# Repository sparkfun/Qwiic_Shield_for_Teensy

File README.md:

# Qwiic_Shield_for_Teensy
This is a shield that connects the I2C bus on a Teensy to Qwiic connectors.

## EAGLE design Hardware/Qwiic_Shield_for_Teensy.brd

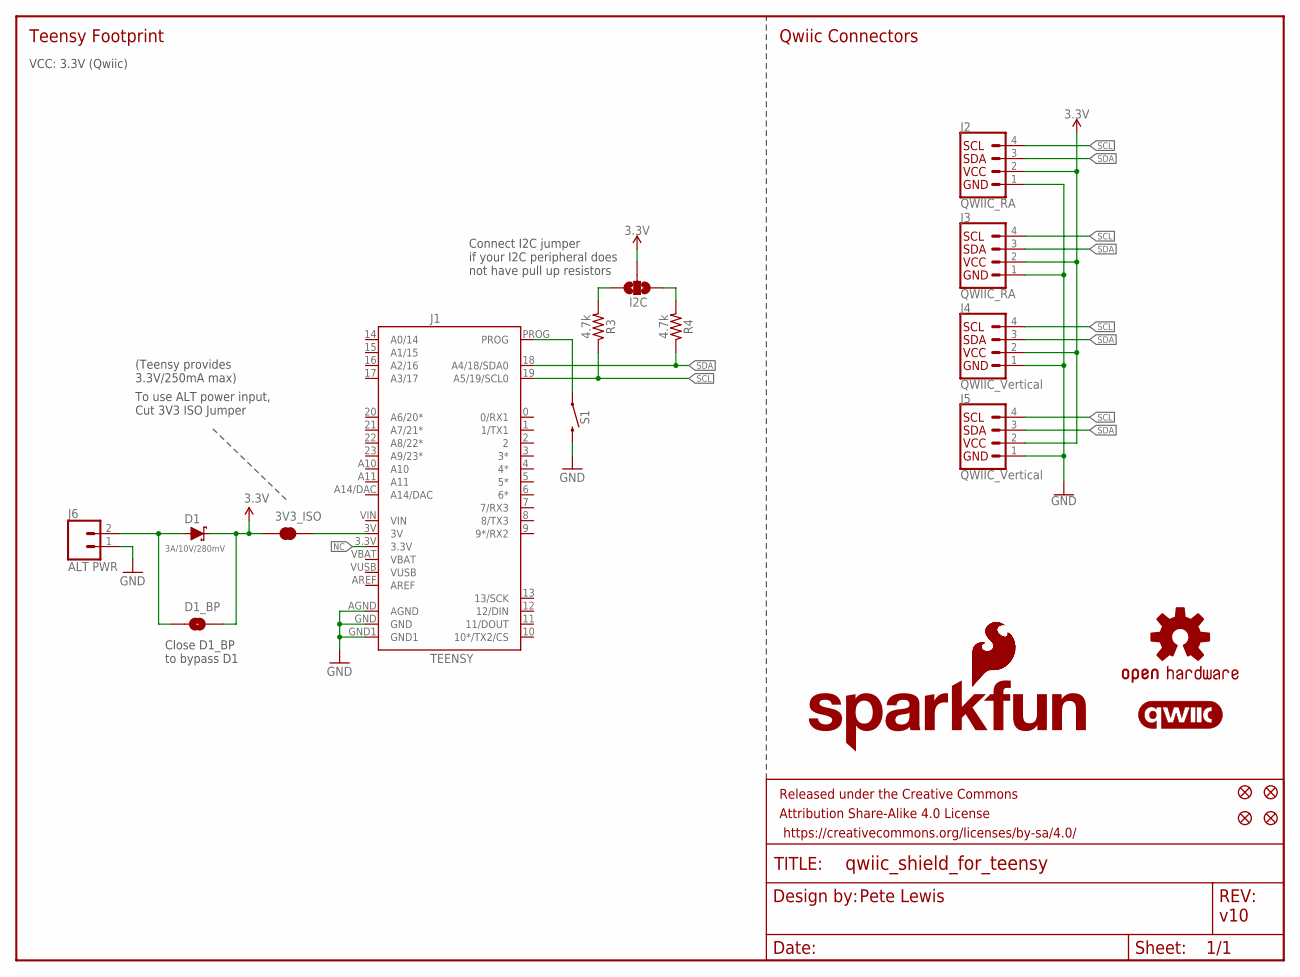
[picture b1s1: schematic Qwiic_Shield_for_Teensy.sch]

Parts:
3V3_ISO: JUMPER-SMT_2_NC_TRACE_SILK; SMT-JUMPER_2_NC_TRACE_SILK
D1: 3A/10V/280mV; SOD-323
D1_BP: JUMPER-SMT_2_NO_SILK; SMT-JUMPER_2_NO_SILK
FD1, FD2, FD3, FD4: FIDUCIAL1X2; FIDUCIAL-1X2
FRAME1: FRAME-LETTER; CREATIVE_COMMONS
I2C: JUMPER-SMT_3_NO_SILK; SMT-JUMPER_3_NO_SILK
J1: TEENSY; TEENSY_NOSILK
J2, J3: QWIIC_RA; JST04_1MM_RA
J4, J5: QWIIC_Vertical; JST04_1MM_VERT
J6: ALT PWR; 1X02_NO_SILK
LOGO1: SFE_LOGO_NAME_FLAME.1_INCH; SFE_LOGO_NAME_FLAME_.1
LOGO2: SFE_LOGO_FLAME.1_INCH; SFE_LOGO_FLAME_.1
LOGO3: OSHW-LOGOS; OSHW-LOGO-S
LOGO4: QWIIC_LOGO_5MM; QWIIC_5MM
R3, R4: 4.7k; 0603
S1: SMD_5.2MM; TACTILE_SWITCH_SMD_5.2MM

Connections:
3.3V: 3V3_ISO.1, D1.C, D1_BP.2, I2C.2, J2.2, J3.2, J4.2, J5.2
GND: J1.AGND, J1.GND, J1.GND1, J2.1, J3.1, J4.1, J5.1, J6.1, S1.3 (2)
unnamed: I2C.3, R4.2
unnamed: I2C.1, R3.2
unnamed: 3V3_ISO.2, J1.3V
unnamed: D1.A, D1_BP.1, J6.2
unnamed: J1.PROG, S1.1
NC: J1.3.3V
SCL: J1.19 (A5/19/SCL0), J2.4, J3.4, J4.4, J5.4, R3.1
SDA: J1.18 (A4/18/SDA0), J2.3, J3.3, J4.3, J5.3, R4.1
VBAT: J1.VBAT
VIN: J1.VIN
VUSB: J1.VUSB

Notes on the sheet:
Pete Lewis
v10
Teensy Footprint
Qwiic Connectors
VCC: 3.3V (Qwiic)
(Teensy provides 3.3V/250mA max)
Connect I2C jumper if your I2C peripheral does not have pull up resistors
To use ALT power input, Cut 3V3 ISO Jumper
Close D1_BP to bypass D1

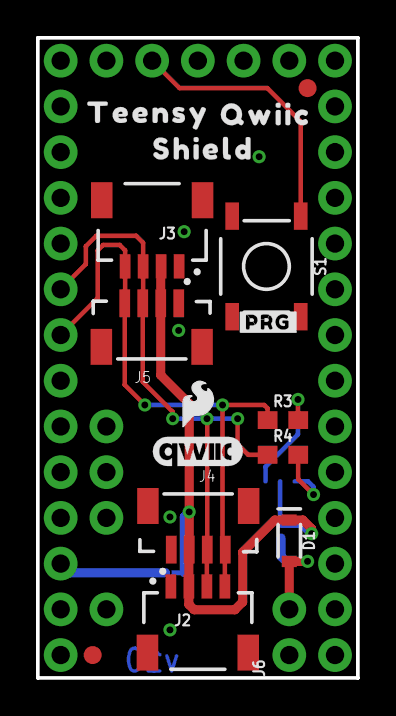
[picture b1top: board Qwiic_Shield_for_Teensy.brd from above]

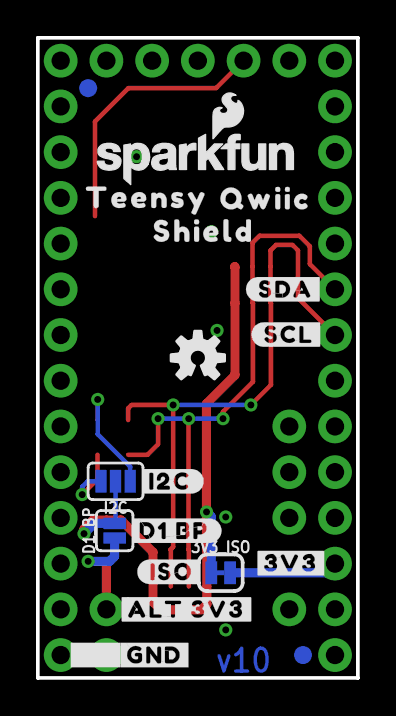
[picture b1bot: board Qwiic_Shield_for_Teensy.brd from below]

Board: 2 copper layers, 17.8 x 35.6 mm, 38 parts (18 on the bottom side), 9 nets.

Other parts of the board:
U$1: #I2C#0
U$2, U$13: TEENSY0
U$3: 3V36
U$4: #D1_BP#0
U$5: #ALT_3V3#0
U$6: #PRG#0
U$7: #GND#0
U$8, U$12: SHIELD0
U$9, U$11: QWIIC0
U$10: #ISO#0
U$15: #3V3#0
U$18: #SDA#0
U$19: #SCL#0

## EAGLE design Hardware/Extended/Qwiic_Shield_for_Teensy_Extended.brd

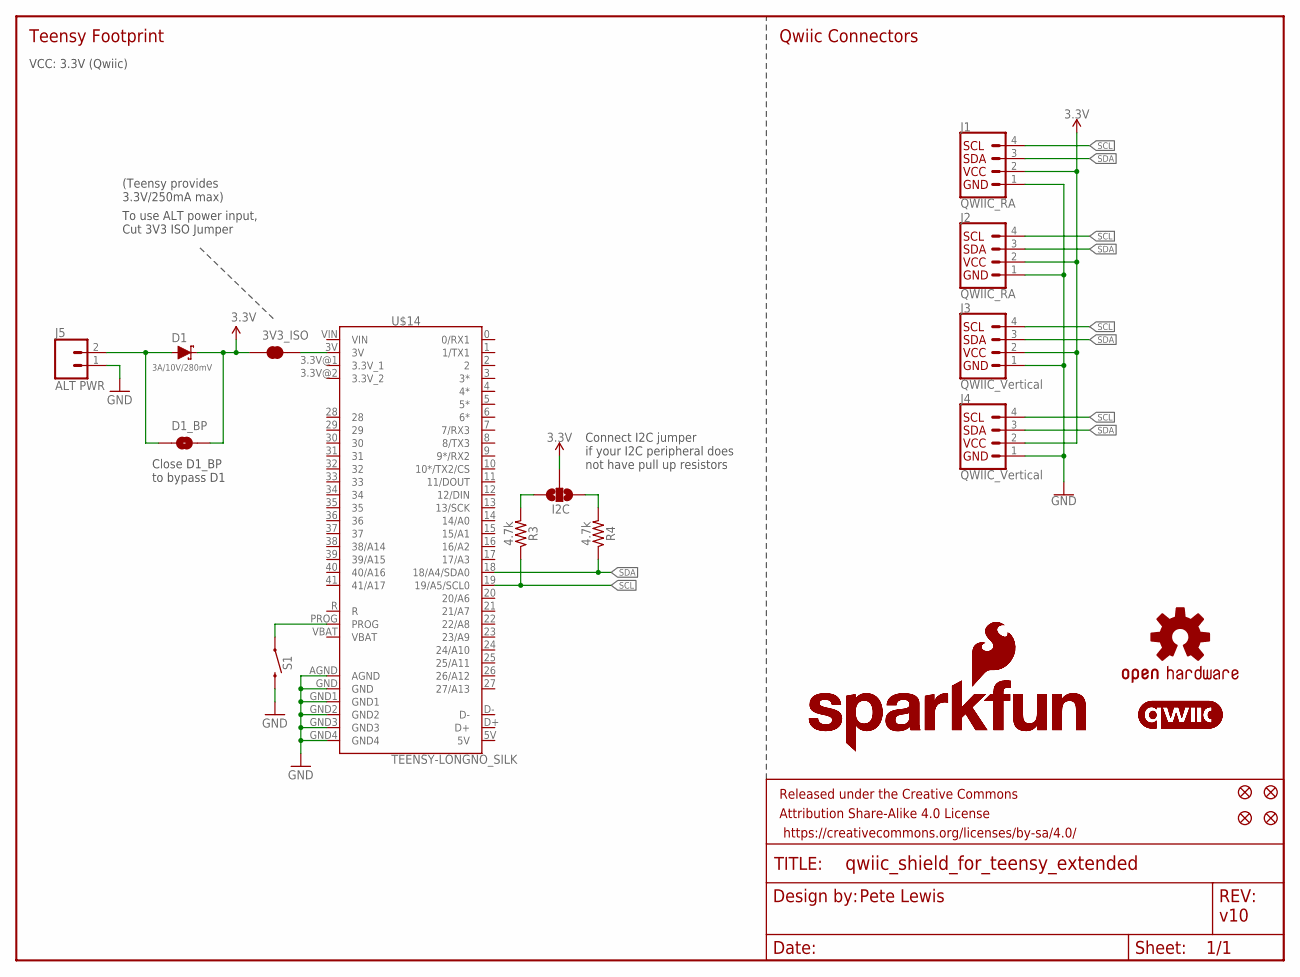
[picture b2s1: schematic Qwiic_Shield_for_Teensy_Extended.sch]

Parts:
3V3_ISO: JUMPER-SMT_2_NC_TRACE_SILK; SMT-JUMPER_2_NC_TRACE_SILK
D1: 3A/10V/280mV; SOD-323
D1_BP: JUMPER-SMT_2_NO_SILK; SMT-JUMPER_2_NO_SILK
FD1, FD2, FD3, FD4: FIDUCIAL1X2; FIDUCIAL-1X2
FRAME1: FRAME-LETTER; CREATIVE_COMMONS
I2C: JUMPER-SMT_3_NO_SILK; SMT-JUMPER_3_NO_SILK
J1, J2: QWIIC_RA; JST04_1MM_RA
J3, J4: QWIIC_Vertical; JST04_1MM_VERT
J5: ALT PWR; 1X02_NO_SILK
LOGO1, LOGO2: SFE_LOGO_NAME_FLAME.1_INCH; SFE_LOGO_NAME_FLAME_.1
LOGO3: OSHW-LOGOS; OSHW-LOGO-S
LOGO4, LOGO5: QWIIC_LOGO_5MM; QWIIC_5MM
R3, R4: 4.7k; 0603
S1: MOMENTARY-SWITCH-SPST-SMD-5.2MM-TALL; TACTILE_SWITCH_SMD_5.2MM
U$14: TEENSY-LONGNO_SILK; TEENSY-LONG_NO_SILK

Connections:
3.3V: 3V3_ISO.1, D1.C, D1_BP.2, I2C.2, J1.2, J2.2, J3.2, J4.2
3.3V_1: U$14.3.3V@1 (3.3V_1)
3.3V_2: U$14.3.3V@2 (3.3V_2)
5V: U$14.5V
D+: U$14.D+
D-: U$14.D-
GND: J1.1, J2.1, J3.1, J4.1, J5.1, S1.3 (2), U$14.AGND, U$14.GND, U$14.GND1, U$14.GND2, U$14.GND3, U$14.GND4
unnamed: I2C.3, R4.2
unnamed: I2C.1, R3.2
unnamed: 3V3_ISO.2, U$14.3V
unnamed: D1.A, D1_BP.1, J5.2
unnamed: S1.1, U$14.PROG
SCL: J1.4, J2.4, J3.4, J4.4, R3.1, U$14.19 (19/A5/SCL0)
SDA: J1.3, J2.3, J3.3, J4.3, R4.1, U$14.18 (18/A4/SDA0)
VBAT: U$14.VBAT
VIN: U$14.VIN

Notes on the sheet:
Pete Lewis
v10
Teensy Footprint
Qwiic Connectors
VCC: 3.3V (Qwiic)
(Teensy provides 3.3V/250mA max)
Connect I2C jumper if your I2C peripheral does not have pull up resistors
To use ALT power input, Cut 3V3 ISO Jumper
Close D1_BP to bypass D1

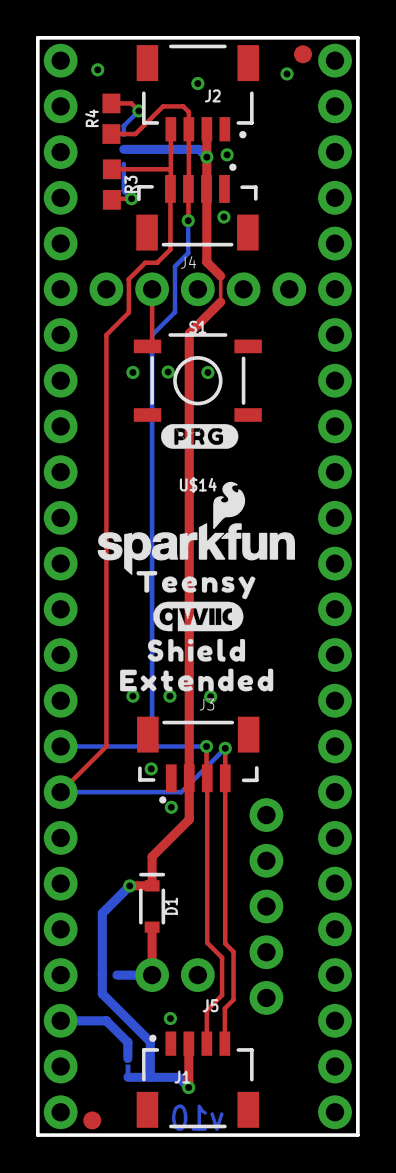
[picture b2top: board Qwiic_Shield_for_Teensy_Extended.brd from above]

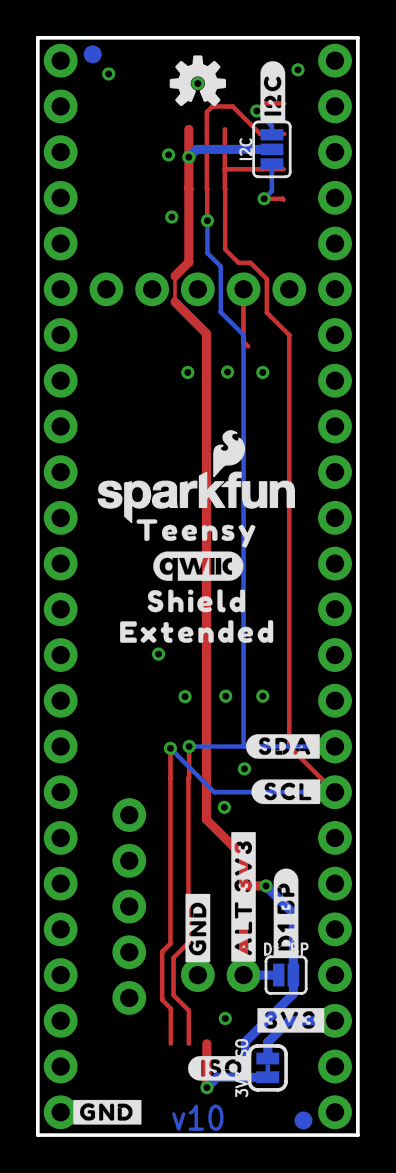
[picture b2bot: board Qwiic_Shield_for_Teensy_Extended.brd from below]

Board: 2 copper layers, 17.8 x 61.0 mm, 40 parts (20 on the bottom side), 9 nets.

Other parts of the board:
U$1: #I2C#0
U$2, U$13: TEENSY0
U$3: 3V36
U$4: #D1_BP#0
U$5: #ALT_3V3#0
U$6: #PRG#0
U$7, U$9: #GND#0
U$8, U$12: SHIELD0
U$10: #ISO#0
U$11, U$16: EXTENDED0
U$15: #3V3#0
U$18: #SDA#0
U$19: #SCL#0

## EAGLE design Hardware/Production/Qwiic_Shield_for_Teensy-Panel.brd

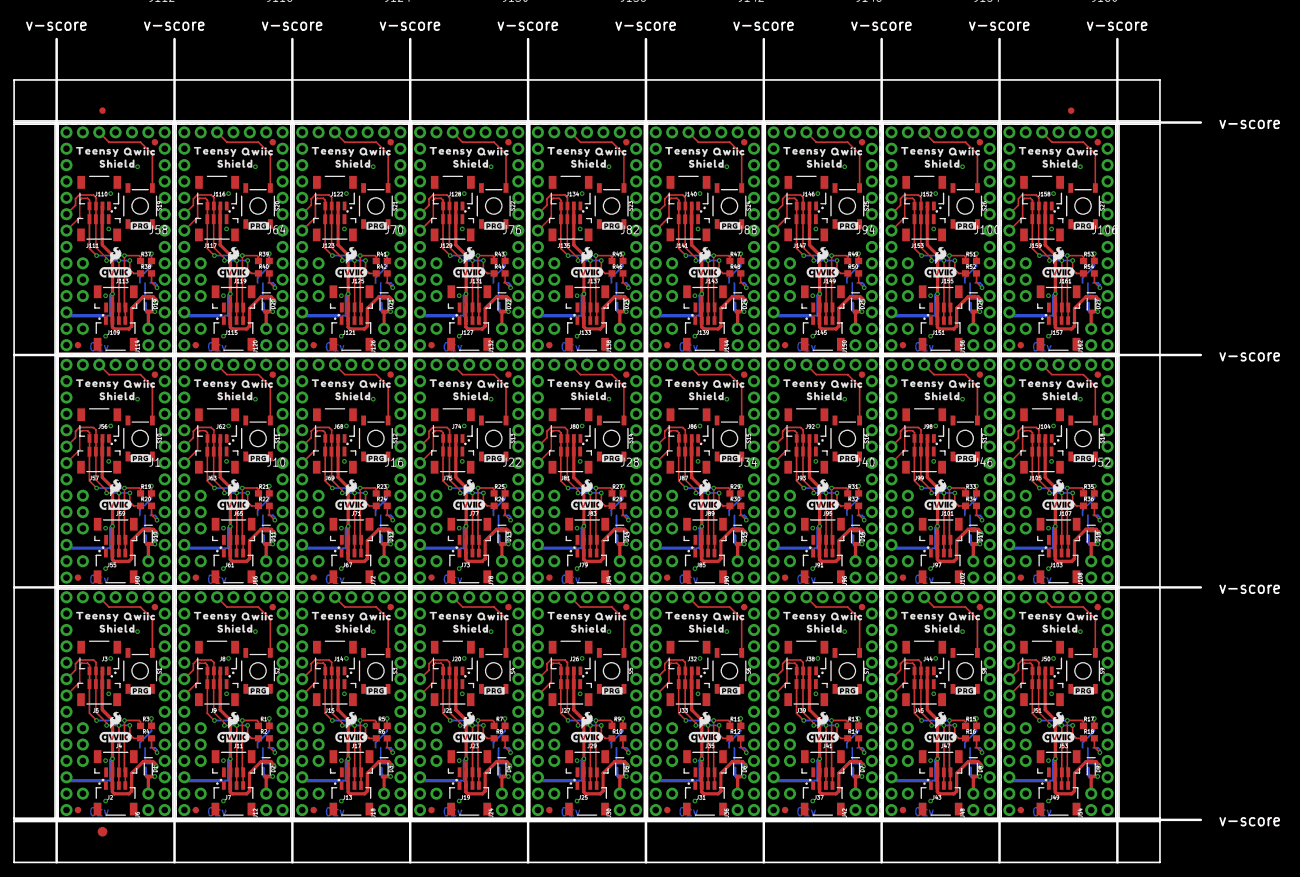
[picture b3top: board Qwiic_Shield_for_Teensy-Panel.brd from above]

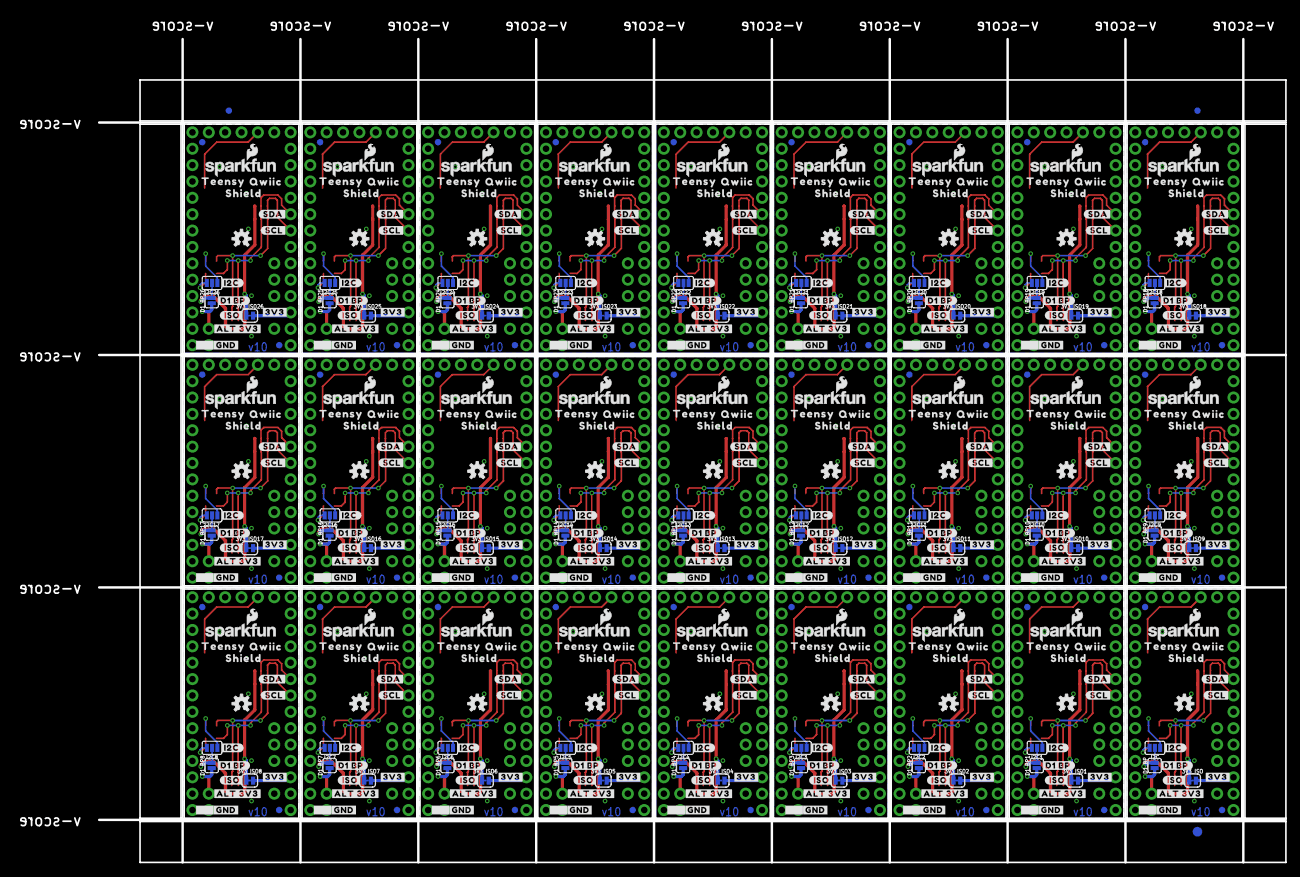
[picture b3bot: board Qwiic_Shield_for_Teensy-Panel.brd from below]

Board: 2 copper layers, 197.3 x 131.6 mm, 1005 parts (489 on the bottom side), 243 nets.

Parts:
3V3_ISO, 3V3_ISO1, 3V3_ISO2, 3V3_ISO3, 3V3_ISO4, 3V3_ISO5, 3V3_ISO6, 3V3_ISO7, 3V3_ISO8, 3V3_ISO9, 3V3_ISO10, 3V3_ISO11, 3V3_ISO12, 3V3_ISO13, 3V3_ISO14, 3V3_ISO15, 3V3_ISO16, 3V3_ISO17, 3V3_ISO18, 3V3_ISO19, 3V3_ISO20, 3V3_ISO21, 3V3_ISO22, 3V3_ISO23, 3V3_ISO24, 3V3_ISO25, 3V3_ISO26: SMT-JUMPER_2_NC_TRACE_SILK
D1, D2, D3, D4, D5, D6, D7, D8, D9, D10, D11, D12, D13, D14, D15, D16, D17, D18, D19, D20, D21, D22, D23, D24, D25, D26, D27: 3A/10V/280mV; SOD-323
D1_BP, D1_BP1, D1_BP2, D1_BP3, D1_BP4, D1_BP5, D1_BP6, D1_BP7, D1_BP8, D1_BP9, D1_BP10, D1_BP11, D1_BP12, D1_BP13, D1_BP14, D1_BP15, D1_BP16, D1_BP17, D1_BP18, D1_BP19, D1_BP20, D1_BP21, D1_BP22, D1_BP23, D1_BP24, D1_BP25, D1_BP26: SMT-JUMPER_2_NO_SILK
E$1, E$2, E$3, E$4: FIDUCIAL-1X2
E$5, E$6: FIDUCIAL-1.5X3
FD1, FD2, FD3, FD4, FD5, FD6, FD7, FD8, FD9, FD10, FD11, FD12, FD13, FD14, FD15, FD16, FD17, FD18, FD19, FD20, FD21, FD22, FD23, FD24, FD25, FD26, FD27, FD28, FD29, FD30, FD31, FD32, FD33, FD34, FD35, FD36, FD37, FD38, FD39, FD40, FD41, FD42, FD43, FD44, FD45, FD46, FD47, FD48, FD49, FD50, FD51, FD52, FD53, FD54, FD55, FD56, FD57, FD58, FD59, FD60, FD61, FD62, FD63, FD64, FD65, FD66, FD67, FD68, FD69, FD70, FD71, FD72, FD73, FD74, FD75, FD76, FD77, FD78, FD79, FD80, FD81, FD82, FD83, FD84, FD85, FD86, FD87, FD88, FD89, FD90, FD91, FD92, FD93, FD94, FD95, FD96, FD97, FD98, FD99, FD100, FD101, FD102, FD103, FD104, FD105, FD106, FD107, FD108: FIDUCIAL1X2; FIDUCIAL-1X2
I2C, I2C1, I2C2, I2C3, I2C4, I2C5, I2C6, I2C7, I2C8, I2C9, I2C10, I2C11, I2C12, I2C13, I2C14, I2C15, I2C16, I2C17, I2C18, I2C19, I2C20, I2C21, I2C22, I2C23, I2C24, I2C25, I2C26: JUMPER-SMT_3_NO_SILK; SMT-JUMPER_3_NO_SILK
J1, J10, J16, J22, J28, J34, J40, J46, J52, J58, J64, J70, J76, J82, J88, J94, J100, J106, J112, J118, J124, J130, J136, J142, J148, J154, J160: TEENSY; TEENSY_NOSILK
J2, J3, J7, J8, J13, J14, J19, J20, J25, J26, J31, J32, J37, J38, J43, J44, J49, J50, J55, J56, J61, J62, J67, J68, J73, J74, J79, J80, J85, J86, J91, J92, J97, J98, J103, J104, J109, J110, J115, J116, J121, J122, J127, J128, J133, J134, J139, J140, J145, J146, J151, J152, J157, J158: QWIIC_RA; JST04_1MM_RA
J4, J5, J9, J11, J15, J17, J21, J23, J27, J29, J33, J35, J39, J41, J45, J47, J51, J53, J57, J59, J63, J65, J69, J71, J75, J77, J81, J83, J87, J89, J93, J95, J99, J101, J105, J107, J111, J113, J117, J119, J123, J125, J129, J131, J135, J137, J141, J143, J147, J149, J153, J155, J159, J161: QWIIC_Vertical; JST04_1MM_VERT
J6, J12, J18, J24, J30, J36, J42, J48, J54, J60, J66, J72, J78, J84, J90, J96, J102, J108, J114, J120, J126, J132, J138, J144, J150, J156, J162: ALT PWR; 1X02_NO_SILK
LOGO1, LOGO5, LOGO9, LOGO13, LOGO17, LOGO21, LOGO25, LOGO29, LOGO33, LOGO37, LOGO41, LOGO45, LOGO49, LOGO53, LOGO57, LOGO61, LOGO65, LOGO69, LOGO73, LOGO77, LOGO81, LOGO85, LOGO89, LOGO93, LOGO97, LOGO101, LOGO105: SFE_LOGO_NAME_FLAME.1_INCH; SFE_LOGO_NAME_FLAME_.1
LOGO2, LOGO8, LOGO12, LOGO16, LOGO20, LOGO24, LOGO28, LOGO32, LOGO36, LOGO40, LOGO44, LOGO48, LOGO52, LOGO56, LOGO60, LOGO64, LOGO68, LOGO72, LOGO76, LOGO80, LOGO84, LOGO88, LOGO92, LOGO96, LOGO100, LOGO104, LOGO108: SFE_LOGO_FLAME.1_INCH; SFE_LOGO_FLAME_.1
LOGO3, LOGO6, LOGO10, LOGO14, LOGO18, LOGO22, LOGO26, LOGO30, LOGO34, LOGO38, LOGO42, LOGO46, LOGO50, LOGO54, LOGO58, LOGO62, LOGO66, LOGO70, LOGO74, LOGO78, LOGO82, LOGO86, LOGO90, LOGO94, LOGO98, LOGO102, LOGO106: OSHW-LOGOS; OSHW-LOGO-S
LOGO4, LOGO7, LOGO11, LOGO15, LOGO19, LOGO23, LOGO27, LOGO31, LOGO35, LOGO39, LOGO43, LOGO47, LOGO51, LOGO55, LOGO59, LOGO63, LOGO67, LOGO71, LOGO75, LOGO79, LOGO83, LOGO87, LOGO91, LOGO95, LOGO99, LOGO103, LOGO107: QWIIC_LOGO_5MM; QWIIC_5MM
R1, R2, R3, R4, R5, R6, R7, R8, R9, R10, R11, R12, R13, R14, R15, R16, R17, R18, R19, R20, R21, R22, R23, R24, R25, R26, R27, R28, R29, R30, R31, R32, R33, R34, R35, R36, R37, R38, R39, R40, R41, R42, R43, R44, R45, R46, R47, R48, R49, R50, R51, R52, R53, R54: 4.7k; 0603
S1, S2, S3, S4, S5, S6, S7, S8, S9, S10, S11, S12, S13, S14, S15, S16, S17, S18, S19, S20, S21, S22, S23, S24, S25, S26, S27: SMD_5.2MM; TACTILE_SWITCH_SMD_5.2MM
U$1, U$22, U$38, U$54, U$70, U$86, U$102, U$118, U$134, U$150, U$166, U$182, U$198, U$214, U$230, U$246, U$262, U$278, U$294, U$310, U$326, U$342, U$358, U$374, U$390, U$406, U$422: #I2C#0
U$2, U$13, U$16, U$30, U$34, U$46, U$50, U$62, U$66, U$78, U$82, U$94, U$98, U$110, U$114, U$126, U$130, U$142, U$146, U$158, U$162, U$174, U$178, U$190, U$194, U$206, U$210, U$222, U$226, U$238, U$242, U$254, U$258, U$270, U$274, U$286, U$290, U$302, U$306, U$318, U$322, U$334, U$338, U$350, U$354, U$366, U$370, U$382, U$386, U$398, U$402, U$414, U$418, U$430: TEENSY0
U$3, U$14, U$33, U$49, U$65, U$81, U$97, U$113, U$129, U$145, U$161, U$177, U$193, U$209, U$225, U$241, U$257, U$273, U$289, U$305, U$321, U$337, U$353, U$369, U$385, U$401, U$417: 3V36
U$4, U$23, U$39, U$55, U$71, U$87, U$103, U$119, U$135, U$151, U$167, U$183, U$199, U$215, U$231, U$247, U$263, U$279, U$295, U$311, U$327, U$343, U$359, U$375, U$391, U$407, U$423: #D1_BP#0
U$5, U$24, U$40, U$56, U$72, U$88, U$104, U$120, U$136, U$152, U$168, U$184, U$200, U$216, U$232, U$248, U$264, U$280, U$296, U$312, U$328, U$344, U$360, U$376, U$392, U$408, U$424: #ALT_3V3#0
U$6, U$28, U$44, U$60, U$76, U$92, U$108, U$124, U$140, U$156, U$172, U$188, U$204, U$220, U$236, U$252, U$268, U$284, U$300, U$316, U$332, U$348, U$364, U$380, U$396, U$412, U$428: #PRG#0
U$7, U$25, U$41, U$57, U$73, U$89, U$105, U$121, U$137, U$153, U$169, U$185, U$201, U$217, U$233, U$249, U$265, U$281, U$297, U$313, U$329, U$345, U$361, U$377, U$393, U$409, U$425: #GND#0
U$8, U$12, U$26, U$32, U$42, U$48, U$58, U$64, U$74, U$80, U$90, U$96, U$106, U$112, U$122, U$128, U$138, U$144, U$154, U$160, U$170, U$176, U$186, U$192, U$202, U$208, U$218, U$224, U$234, U$240, U$250, U$256, U$266, U$272, U$282, U$288, U$298, U$304, U$314, U$320, U$330, U$336, U$346, U$352, U$362, U$368, U$378, U$384, U$394, U$400, U$410, U$416, U$426, U$432: SHIELD0
U$9, U$11, U$27, U$31, U$43, U$47, U$59, U$63, U$75, U$79, U$91, U$95, U$107, U$111, U$123, U$127, U$139, U$143, U$155, U$159, U$171, U$175, U$187, U$191, U$203, U$207, U$219, U$223, U$235, U$239, U$251, U$255, U$267, U$271, U$283, U$287, U$299, U$303, U$315, U$319, U$331, U$335, U$347, U$351, U$363, U$367, U$379, U$383, U$395, U$399, U$411, U$415, U$427, U$431: QWIIC0
U$10, U$29, U$45, U$61, U$77, U$93, U$109, U$125, U$141, U$157, U$173, U$189, U$205, U$221, U$237, U$253, U$269, U$285, U$301, U$317, U$333, U$349, U$365, U$381, U$397, U$413, U$429: #ISO#0
U$15, U$17, U$35, U$51, U$67, U$83, U$99, U$115, U$131, U$147, U$163, U$179, U$195, U$211, U$227, U$243, U$259, U$275, U$291, U$307, U$323, U$339, U$355, U$371, U$387, U$403, U$419: #3V3#0
U$18, U$20, U$36, U$52, U$68, U$84, U$100, U$116, U$132, U$148, U$164, U$180, U$196, U$212, U$228, U$244, U$260, U$276, U$292, U$308, U$324, U$340, U$356, U$372, U$388, U$404, U$420: #SDA#0
U$19, U$21, U$37, U$53, U$69, U$85, U$101, U$117, U$133, U$149, U$165, U$181, U$197, U$213, U$229, U$245, U$261, U$277, U$293, U$309, U$325, U$341, U$357, U$373, U$389, U$405, U$421: #SCL#0

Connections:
3.3V: 3V3_ISO.1, D1.C, D1_BP.2, I2C.2, J2.2, J3.2, J4.2, J5.2
3.3V1: 3V3_ISO1.1, D1_BP1.2, D2.C, I2C1.2, J7.2, J8.2, J9.2, J11.2
3.3V2: 3V3_ISO2.1, D1_BP2.2, D3.C, I2C2.2, J13.2, J14.2, J15.2, J17.2
3.3V3: 3V3_ISO3.1, D1_BP3.2, D4.C, I2C3.2, J19.2, J20.2, J21.2, J23.2
3.3V4: 3V3_ISO4.1, D1_BP4.2, D5.C, I2C4.2, J25.2, J26.2, J27.2, J29.2
3.3V5: 3V3_ISO5.1, D1_BP5.2, D6.C, I2C5.2, J31.2, J32.2, J33.2, J35.2
3.3V6: 3V3_ISO6.1, D1_BP6.2, D7.C, I2C6.2, J37.2, J38.2, J39.2, J41.2
3.3V7: 3V3_ISO7.1, D1_BP7.2, D8.C, I2C7.2, J43.2, J44.2, J45.2, J47.2
3.3V8: 3V3_ISO8.1, D1_BP8.2, D9.C, I2C8.2, J49.2, J50.2, J51.2, J53.2
3.3V9: 3V3_ISO9.1, D1_BP9.2, D10.C, I2C9.2, J55.2, J56.2, J57.2, J59.2
3.3V10: 3V3_ISO10.1, D1_BP10.2, D11.C, I2C10.2, J61.2, J62.2, J63.2, J65.2
3.3V11: 3V3_ISO11.1, D1_BP11.2, D12.C, I2C11.2, J67.2, J68.2, J69.2, J71.2
3.3V12: 3V3_ISO12.1, D1_BP12.2, D13.C, I2C12.2, J73.2, J74.2, J75.2, J77.2
3.3V13: 3V3_ISO13.1, D1_BP13.2, D14.C, I2C13.2, J79.2, J80.2, J81.2, J83.2
3.3V14: 3V3_ISO14.1, D1_BP14.2, D15.C, I2C14.2, J85.2, J86.2, J87.2, J89.2
3.3V15: 3V3_ISO15.1, D1_BP15.2, D16.C, I2C15.2, J91.2, J92.2, J93.2, J95.2
3.3V16: 3V3_ISO16.1, D1_BP16.2, D17.C, I2C16.2, J97.2, J98.2, J99.2, J101.2
3.3V17: 3V3_ISO17.1, D1_BP17.2, D18.C, I2C17.2, J103.2, J104.2, J105.2, J107.2
3.3V18: 3V3_ISO18.1, D1_BP18.2, D19.C, I2C18.2, J109.2, J110.2, J111.2, J113.2
3.3V19: 3V3_ISO19.1, D1_BP19.2, D20.C, I2C19.2, J115.2, J116.2, J117.2, J119.2
3.3V20: 3V3_ISO20.1, D1_BP20.2, D21.C, I2C20.2, J121.2, J122.2, J123.2, J125.2
3.3V21: 3V3_ISO21.1, D1_BP21.2, D22.C, I2C21.2, J127.2, J128.2, J129.2, J131.2
3.3V22: 3V3_ISO22.1, D1_BP22.2, D23.C, I2C22.2, J133.2, J134.2, J135.2, J137.2
3.3V23: 3V3_ISO23.1, D1_BP23.2, D24.C, I2C23.2, J139.2, J140.2, J141.2, J143.2
3.3V24: 3V3_ISO24.1, D1_BP24.2, D25.C, I2C24.2, J145.2, J146.2, J147.2, J149.2
3.3V25: 3V3_ISO25.1, D1_BP25.2, D26.C, I2C25.2, J151.2, J152.2, J153.2, J155.2
3.3V26: 3V3_ISO26.1, D1_BP26.2, D27.C, I2C26.2, J157.2, J158.2, J159.2, J161.2
GND: J1.AGND, J1.GND, J1.GND1, J2.1, J3.1, J4.1, J5.1, J6.1, S1.3
GND1: J7.1, J8.1, J9.1, J10.AGND, J10.GND, J10.GND1, J11.1, J12.1, S2.3
GND2: J13.1, J14.1, J15.1, J16.AGND, J16.GND, J16.GND1, J17.1, J18.1, S3.3
GND3: J19.1, J20.1, J21.1, J22.AGND, J22.GND, J22.GND1, J23.1, J24.1, S4.3
GND4: J25.1, J26.1, J27.1, J28.AGND, J28.GND, J28.GND1, J29.1, J30.1, S5.3
GND5: J31.1, J32.1, J33.1, J34.AGND, J34.GND, J34.GND1, J35.1, J36.1, S6.3
GND6: J37.1, J38.1, J39.1, J40.AGND, J40.GND, J40.GND1, J41.1, J42.1, S7.3
GND7: J43.1, J44.1, J45.1, J46.AGND, J46.GND, J46.GND1, J47.1, J48.1, S8.3
GND8: J49.1, J50.1, J51.1, J52.AGND, J52.GND, J52.GND1, J53.1, J54.1, S9.3
GND9: J55.1, J56.1, J57.1, J58.AGND, J58.GND, J58.GND1, J59.1, J60.1, S10.3
GND10: J61.1, J62.1, J63.1, J64.AGND, J64.GND, J64.GND1, J65.1, J66.1, S11.3
GND11: J67.1, J68.1, J69.1, J70.AGND, J70.GND, J70.GND1, J71.1, J72.1, S12.3
GND12: J73.1, J74.1, J75.1, J76.AGND, J76.GND, J76.GND1, J77.1, J78.1, S13.3
GND13: J79.1, J80.1, J81.1, J82.AGND, J82.GND, J82.GND1, J83.1, J84.1, S14.3
GND14: J85.1, J86.1, J87.1, J88.AGND, J88.GND, J88.GND1, J89.1, J90.1, S15.3
GND15: J91.1, J92.1, J93.1, J94.AGND, J94.GND, J94.GND1, J95.1, J96.1, S16.3
GND16: J97.1, J98.1, J99.1, J100.AGND, J100.GND, J100.GND1, J101.1, J102.1, S17.3
GND17: J103.1, J104.1, J105.1, J106.AGND, J106.GND, J106.GND1, J107.1, J108.1, S18.3
GND18: J109.1, J110.1, J111.1, J112.AGND, J112.GND, J112.GND1, J113.1, J114.1, S19.3
GND19: J115.1, J116.1, J117.1, J118.AGND, J118.GND, J118.GND1, J119.1, J120.1, S20.3
GND20: J121.1, J122.1, J123.1, J124.AGND, J124.GND, J124.GND1, J125.1, J126.1, S21.3
GND21: J127.1, J128.1, J129.1, J130.AGND, J130.GND, J130.GND1, J131.1, J132.1, S22.3
GND22: J133.1, J134.1, J135.1, J136.AGND, J136.GND, J136.GND1, J137.1, J138.1, S23.3
GND23: J139.1, J140.1, J141.1, J142.AGND, J142.GND, J142.GND1, J143.1, J144.1, S24.3
GND24: J145.1, J146.1, J147.1, J148.AGND, J148.GND, J148.GND1, J149.1, J150.1, S25.3
GND25: J151.1, J152.1, J153.1, J154.AGND, J154.GND, J154.GND1, J155.1, J156.1, S26.3
GND26: J157.1, J158.1, J159.1, J160.AGND, J160.GND, J160.GND1, J161.1, J162.1, S27.3
unnamed: I2C.3, R4.2
unnamed: I2C.1, R3.2
unnamed: 3V3_ISO.2, J1.3V
unnamed: D1.A, D1_BP.1, J6.2
unnamed: J1.PROG, S1.1
unnamed: I2C1.3, R2.2
unnamed: I2C1.1, R1.2
unnamed: D1_BP1.1, D2.A, J12.2
unnamed: J10.PROG, S2.1
unnamed: 3V3_ISO1.2, J10.3V
unnamed: I2C2.3, R6.2
unnamed: I2C2.1, R5.2
unnamed: D1_BP2.1, D3.A, J18.2
unnamed: J16.PROG, S3.1
unnamed: 3V3_ISO2.2, J16.3V
unnamed: I2C3.3, R8.2
unnamed: I2C3.1, R7.2
unnamed: D1_BP3.1, D4.A, J24.2
unnamed: J22.PROG, S4.1
unnamed: 3V3_ISO3.2, J22.3V
unnamed: I2C4.3, R10.2
unnamed: I2C4.1, R9.2
unnamed: D1_BP4.1, D5.A, J30.2
unnamed: J28.PROG, S5.1
unnamed: 3V3_ISO4.2, J28.3V
unnamed: I2C5.3, R12.2
unnamed: I2C5.1, R11.2
unnamed: D1_BP5.1, D6.A, J36.2
unnamed: J34.PROG, S6.1
unnamed: 3V3_ISO5.2, J34.3V
unnamed: I2C6.3, R14.2
unnamed: I2C6.1, R13.2
unnamed: D1_BP6.1, D7.A, J42.2
unnamed: J40.PROG, S7.1
unnamed: 3V3_ISO6.2, J40.3V
unnamed: I2C7.3, R16.2
unnamed: I2C7.1, R15.2
unnamed: D1_BP7.1, D8.A, J48.2
unnamed: J46.PROG, S8.1
unnamed: 3V3_ISO7.2, J46.3V
unnamed: I2C8.3, R18.2
unnamed: I2C8.1, R17.2
unnamed: D1_BP8.1, D9.A, J54.2
unnamed: J52.PROG, S9.1
unnamed: 3V3_ISO8.2, J52.3V
unnamed: I2C9.3, R20.2
unnamed: I2C9.1, R19.2
unnamed: D1_BP9.1, D10.A, J60.2
unnamed: J58.PROG, S10.1
unnamed: 3V3_ISO9.2, J58.3V
unnamed: I2C10.3, R22.2
unnamed: I2C10.1, R21.2
unnamed: D1_BP10.1, D11.A, J66.2
unnamed: J64.PROG, S11.1
unnamed: 3V3_ISO10.2, J64.3V
unnamed: I2C11.3, R24.2
unnamed: I2C11.1, R23.2
unnamed: D1_BP11.1, D12.A, J72.2
unnamed: J70.PROG, S12.1
unnamed: 3V3_ISO11.2, J70.3V
unnamed: I2C12.3, R26.2
unnamed: I2C12.1, R25.2
unnamed: D1_BP12.1, D13.A, J78.2
unnamed: J76.PROG, S13.1
unnamed: 3V3_ISO12.2, J76.3V
unnamed: I2C13.3, R28.2
unnamed: I2C13.1, R27.2
unnamed: D1_BP13.1, D14.A, J84.2
unnamed: J82.PROG, S14.1
unnamed: 3V3_ISO13.2, J82.3V
unnamed: I2C14.3, R30.2
unnamed: I2C14.1, R29.2
unnamed: D1_BP14.1, D15.A, J90.2
unnamed: J88.PROG, S15.1
unnamed: 3V3_ISO14.2, J88.3V
unnamed: I2C15.3, R32.2
unnamed: I2C15.1, R31.2
unnamed: D1_BP15.1, D16.A, J96.2
unnamed: J94.PROG, S16.1
unnamed: 3V3_ISO15.2, J94.3V
unnamed: I2C16.3, R34.2
unnamed: I2C16.1, R33.2
unnamed: D1_BP16.1, D17.A, J102.2
unnamed: J100.PROG, S17.1
unnamed: 3V3_ISO16.2, J100.3V
unnamed: I2C17.3, R36.2
unnamed: I2C17.1, R35.2
unnamed: D1_BP17.1, D18.A, J108.2
unnamed: J106.PROG, S18.1
unnamed: 3V3_ISO17.2, J106.3V
unnamed: I2C18.3, R38.2
unnamed: I2C18.1, R37.2
unnamed: D1_BP18.1, D19.A, J114.2
unnamed: J112.PROG, S19.1
unnamed: 3V3_ISO18.2, J112.3V
unnamed: I2C19.3, R40.2
unnamed: I2C19.1, R39.2
unnamed: D1_BP19.1, D20.A, J120.2
unnamed: J118.PROG, S20.1
unnamed: 3V3_ISO19.2, J118.3V
unnamed: I2C20.3, R42.2
unnamed: I2C20.1, R41.2
unnamed: D1_BP20.1, D21.A, J126.2
unnamed: J124.PROG, S21.1
unnamed: 3V3_ISO20.2, J124.3V
unnamed: I2C21.3, R44.2
unnamed: I2C21.1, R43.2
unnamed: D1_BP21.1, D22.A, J132.2
unnamed: J130.PROG, S22.1
unnamed: 3V3_ISO21.2, J130.3V
unnamed: I2C22.3, R46.2
unnamed: I2C22.1, R45.2
unnamed: D1_BP22.1, D23.A, J138.2
unnamed: J136.PROG, S23.1
unnamed: 3V3_ISO22.2, J136.3V
unnamed: I2C23.3, R48.2
unnamed: I2C23.1, R47.2
unnamed: D1_BP23.1, D24.A, J144.2
unnamed: J142.PROG, S24.1
unnamed: 3V3_ISO23.2, J142.3V
unnamed: I2C24.3, R50.2
unnamed: I2C24.1, R49.2
unnamed: D1_BP24.1, D25.A, J150.2
unnamed: J148.PROG, S25.1
unnamed: 3V3_ISO24.2, J148.3V
unnamed: I2C25.3, R52.2
unnamed: I2C25.1, R51.2
unnamed: D1_BP25.1, D26.A, J156.2
unnamed: J154.PROG, S26.1
unnamed: 3V3_ISO25.2, J154.3V
unnamed: I2C26.3, R54.2
unnamed: I2C26.1, R53.2
unnamed: D1_BP26.1, D27.A, J162.2
unnamed: J160.PROG, S27.1
unnamed: 3V3_ISO26.2, J160.3V
SCL: J1.19, J2.4, J3.4, J4.4, J5.4, R3.1
SCL1: J7.4, J8.4, J9.4, J10.19, J11.4, R1.1
SCL2: J13.4, J14.4, J15.4, J16.19, J17.4, R5.1
SCL3: J19.4, J20.4, J21.4, J22.19, J23.4, R7.1
SCL4: J25.4, J26.4, J27.4, J28.19, J29.4, R9.1
SCL5: J31.4, J32.4, J33.4, J34.19, J35.4, R11.1
SCL6: J37.4, J38.4, J39.4, J40.19, J41.4, R13.1
SCL7: J43.4, J44.4, J45.4, J46.19, J47.4, R15.1
SCL8: J49.4, J50.4, J51.4, J52.19, J53.4, R17.1
SCL9: J55.4, J56.4, J57.4, J58.19, J59.4, R19.1
SCL10: J61.4, J62.4, J63.4, J64.19, J65.4, R21.1
SCL11: J67.4, J68.4, J69.4, J70.19, J71.4, R23.1
SCL12: J73.4, J74.4, J75.4, J76.19, J77.4, R25.1
SCL13: J79.4, J80.4, J81.4, J82.19, J83.4, R27.1
SCL14: J85.4, J86.4, J87.4, J88.19, J89.4, R29.1
SCL15: J91.4, J92.4, J93.4, J94.19, J95.4, R31.1
SCL16: J97.4, J98.4, J99.4, J100.19, J101.4, R33.1
SCL17: J103.4, J104.4, J105.4, J106.19, J107.4, R35.1
SCL18: J109.4, J110.4, J111.4, J112.19, J113.4, R37.1
SCL19: J115.4, J116.4, J117.4, J118.19, J119.4, R39.1
SCL20: J121.4, J122.4, J123.4, J124.19, J125.4, R41.1
SCL21: J127.4, J128.4, J129.4, J130.19, J131.4, R43.1
SCL22: J133.4, J134.4, J135.4, J136.19, J137.4, R45.1
SCL23: J139.4, J140.4, J141.4, J142.19, J143.4, R47.1
SCL24: J145.4, J146.4, J147.4, J148.19, J149.4, R49.1
SCL25: J151.4, J152.4, J153.4, J154.19, J155.4, R51.1
SCL26: J157.4, J158.4, J159.4, J160.19, J161.4, R53.1
SDA: J1.18, J2.3, J3.3, J4.3, J5.3, R4.1
SDA1: J7.3, J8.3, J9.3, J10.18, J11.3, R2.1
SDA2: J13.3, J14.3, J15.3, J16.18, J17.3, R6.1
SDA3: J19.3, J20.3, J21.3, J22.18, J23.3, R8.1
SDA4: J25.3, J26.3, J27.3, J28.18, J29.3, R10.1
SDA5: J31.3, J32.3, J33.3, J34.18, J35.3, R12.1
SDA6: J37.3, J38.3, J39.3, J40.18, J41.3, R14.1
SDA7: J43.3, J44.3, J45.3, J46.18, J47.3, R16.1
SDA8: J49.3, J50.3, J51.3, J52.18, J53.3, R18.1
SDA9: J55.3, J56.3, J57.3, J58.18, J59.3, R20.1
SDA10: J61.3, J62.3, J63.3, J64.18, J65.3, R22.1
SDA11: J67.3, J68.3, J69.3, J70.18, J71.3, R24.1
SDA12: J73.3, J74.3, J75.3, J76.18, J77.3, R26.1
SDA13: J79.3, J80.3, J81.3, J82.18, J83.3, R28.1
SDA14: J85.3, J86.3, J87.3, J88.18, J89.3, R30.1
SDA15: J91.3, J92.3, J93.3, J94.18, J95.3, R32.1
SDA16: J97.3, J98.3, J99.3, J100.18, J101.3, R34.1
SDA17: J103.3, J104.3, J105.3, J106.18, J107.3, R36.1
SDA18: J109.3, J110.3, J111.3, J112.18, J113.3, R38.1
SDA19: J115.3, J116.3, J117.3, J118.18, J119.3, R40.1
SDA20: J121.3, J122.3, J123.3, J124.18, J125.3, R42.1
SDA21: J127.3, J128.3, J129.3, J130.18, J131.3, R44.1
SDA22: J133.3, J134.3, J135.3, J136.18, J137.3, R46.1
SDA23: J139.3, J140.3, J141.3, J142.18, J143.3, R48.1
SDA24: J145.3, J146.3, J147.3, J148.18, J149.3, R50.1
SDA25: J151.3, J152.3, J153.3, J154.18, J155.3, R52.1
SDA26: J157.3, J158.3, J159.3, J160.18, J161.3, R54.1

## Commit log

2020-08-20 ready for routing
2020-08-24 Routing done
    -added diode on ALT 3V3 input
    -added PRG button for easier access to programming button
    -added prototyping area (with vscore) to extend this to also fit longer teensy board form factors
2020-08-24 fixed tiny airwire
2020-08-24 added measures
2020-08-24 Teensy FP library update
2020-08-25 DRC approvals, label adjustments
    -bumped GND pour isolates to 0.008 inch. This allows AREF pin to still get flowed gnd.
    -approved DRC errors about dimension on vscore line
    -fixed some angled traces.
    -removed some trace stubs
    -rotated SDA and SCL to match orientation of other labels
    -ensures all labels were size 0.04
2020-08-25 checklist run pre group review
    -sch fonts to vector
    -via nudges to clear silk
2020-08-31 Post group review changes - short version
    -"slave" terminology needs to be updated to "I2C peripheral"
    -Moving to two separate products. One short and one long. Resolves the prog button access pin difference. no vscores.
    -Switch up qwiic connector positions so that the north RA connector doesn't conflict with the prog button.
    -3.3V power should come from the PTH header pin on the side (not the middle row).
    -Added teensy qwiic shield product name to bottom silk
2020-08-31 teensy long started
    library work and part placement mostly done. ready for routing.
2020-09-01 Long version routed
2020-09-01 Moving to "extended" product name
    -Eagle file name change (and sub-folder)
    -added silk to extended version
2020-09-02 Library updates, name prefix fix, measures update
2020-09-02 separating repo into "normal" and extended versions
2020-09-02 checklist run post design review
    -approved DRC overlap and clearance errors.
    -one small trace nudge to remove one extra unecessary kink
    -part name text adjustments for assembly sheet
2020-09-03 measures correction
    -added x measure for bottom centered qwiic connector
2020-09-04 production panel v10
2020-09-04 added panel dimemsions x and y to panel brd file
2020-09-10 Dimensional drawings
2020-10-13 Update README
    Updating README with photos and links for initial release.
2020-11-05 Migrating teensy part to SparkFun-Boards.lbr
    -migrated teensy device from private mini library into public SparkFun-Boards.lbr
    -replaced part
    -deleted mini library in this repo

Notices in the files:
parts and their libraries:
SparkFun-Aesthetics: Licensing: Creative Commons ShareAlike 4.0 International - https://creativecommons.org/licenses/by-sa/4.0
SparkFun-Aesthetics: Released under the Creative Commons Attribution Share-Alike 4.0 License
SparkFun-Aesthetics: https://creativecommons.org/licenses/by-sa/4.0
